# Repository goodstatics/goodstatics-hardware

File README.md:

# goodstatics-hardware
## Hardware Files for goodstatics PCB

This repository contains all the KiCad and Gerber files necessary for ordering a goodstatics PCB. These may not be designed in the best way, or even function. Look at the schematics and gerber files before ordering.

As for manufacturing, this PCB shouldn't need any special treatment or care from the factory. Order with any finish you like.

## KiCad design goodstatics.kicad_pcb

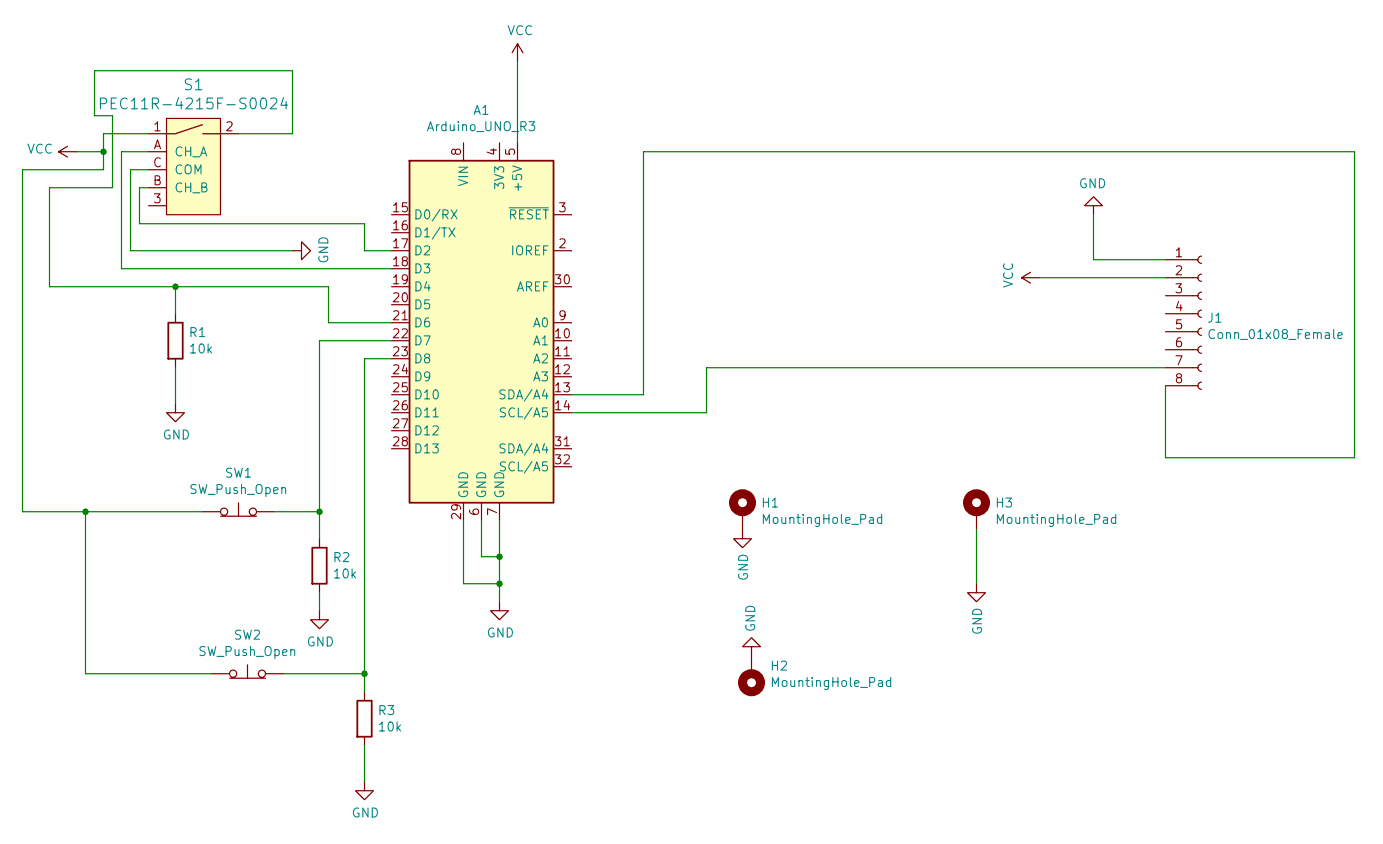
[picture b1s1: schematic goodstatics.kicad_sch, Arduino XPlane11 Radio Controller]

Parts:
A1: Arduino_UNO_R3
H1, H2, H3: MountingHole_Pad; MountingHole_2.5mm_Pad
J1: Conn_01x08_Female; Adafruit_SSD1306
R1, R2, R3: 10k; R_Axial_DIN0204_L3.6mm_D1.6mm_P5.08mm_Vertical
S1: PEC11R-4215F-S0024; Rotary_Encoder_Switched_PEC11R; MPN PEC11R-4215F-S0024; Digi-Key_PN PEC11R-4215F-S0024-ND
SW1, SW2: SW_Push_Open; SW_PUSH_6mm_H4.3mm

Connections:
GND: A1.6 (GND), A1.7 (GND), A1.29 (GND), H1.1, H2.1, H3.1, J1.1, R1.2, R2.2, R3.2, S1.C (COM)
unnamed: A1.13 (SDA/A4), J1.8
unnamed: A1.14 (SCL/A5), J1.7
unnamed: A1.17 (D2), S1.B (CH_B)
unnamed: A1.18 (D3), S1.A (CH_A)
unnamed: A1.21 (D6), R1.1, S1.2
unnamed: A1.22 (D7), R2.1, SW1.2 (B)
unnamed: A1.23 (D8), R3.1, SW2.2 (B)
VCC: A1.5 (+5V), J1.2, S1.1, SW1.1 (A), SW2.1 (A)

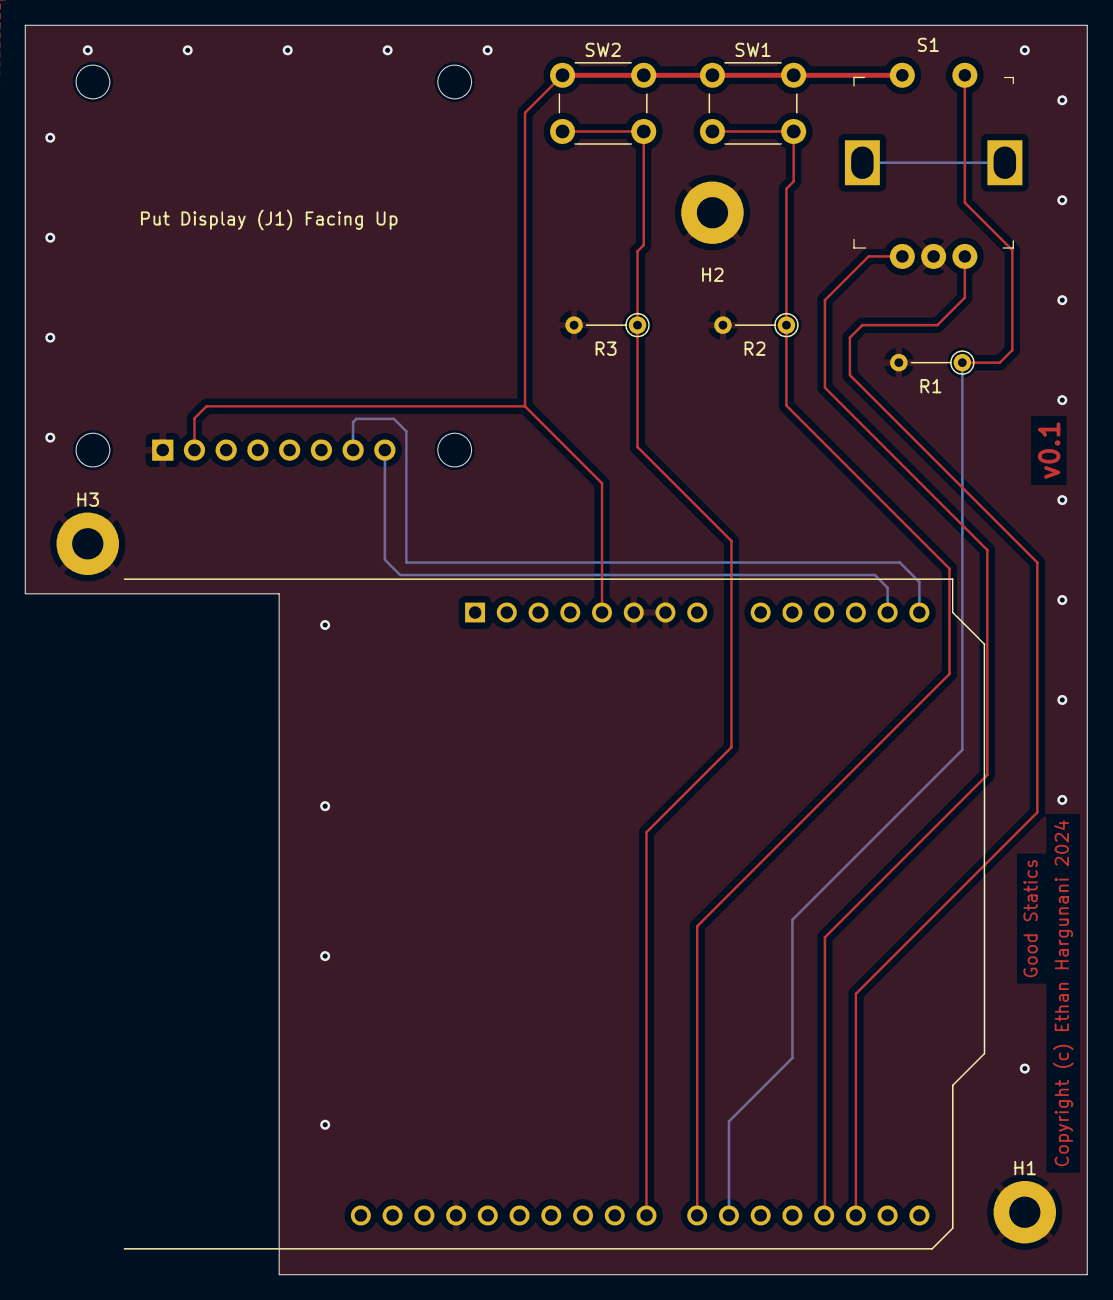
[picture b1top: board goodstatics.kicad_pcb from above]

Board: 2 copper layers, 85.0 x 100.0 mm, 11 parts (1 on the bottom side), 9 nets.

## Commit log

2024-10-28 Create LICENSE
2024-10-28 added hardware files
2024-10-28 Added basic info to README.md

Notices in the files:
goodstatics.kicad_pcb:
Copyright (c) Ethan Hargunani 2024
